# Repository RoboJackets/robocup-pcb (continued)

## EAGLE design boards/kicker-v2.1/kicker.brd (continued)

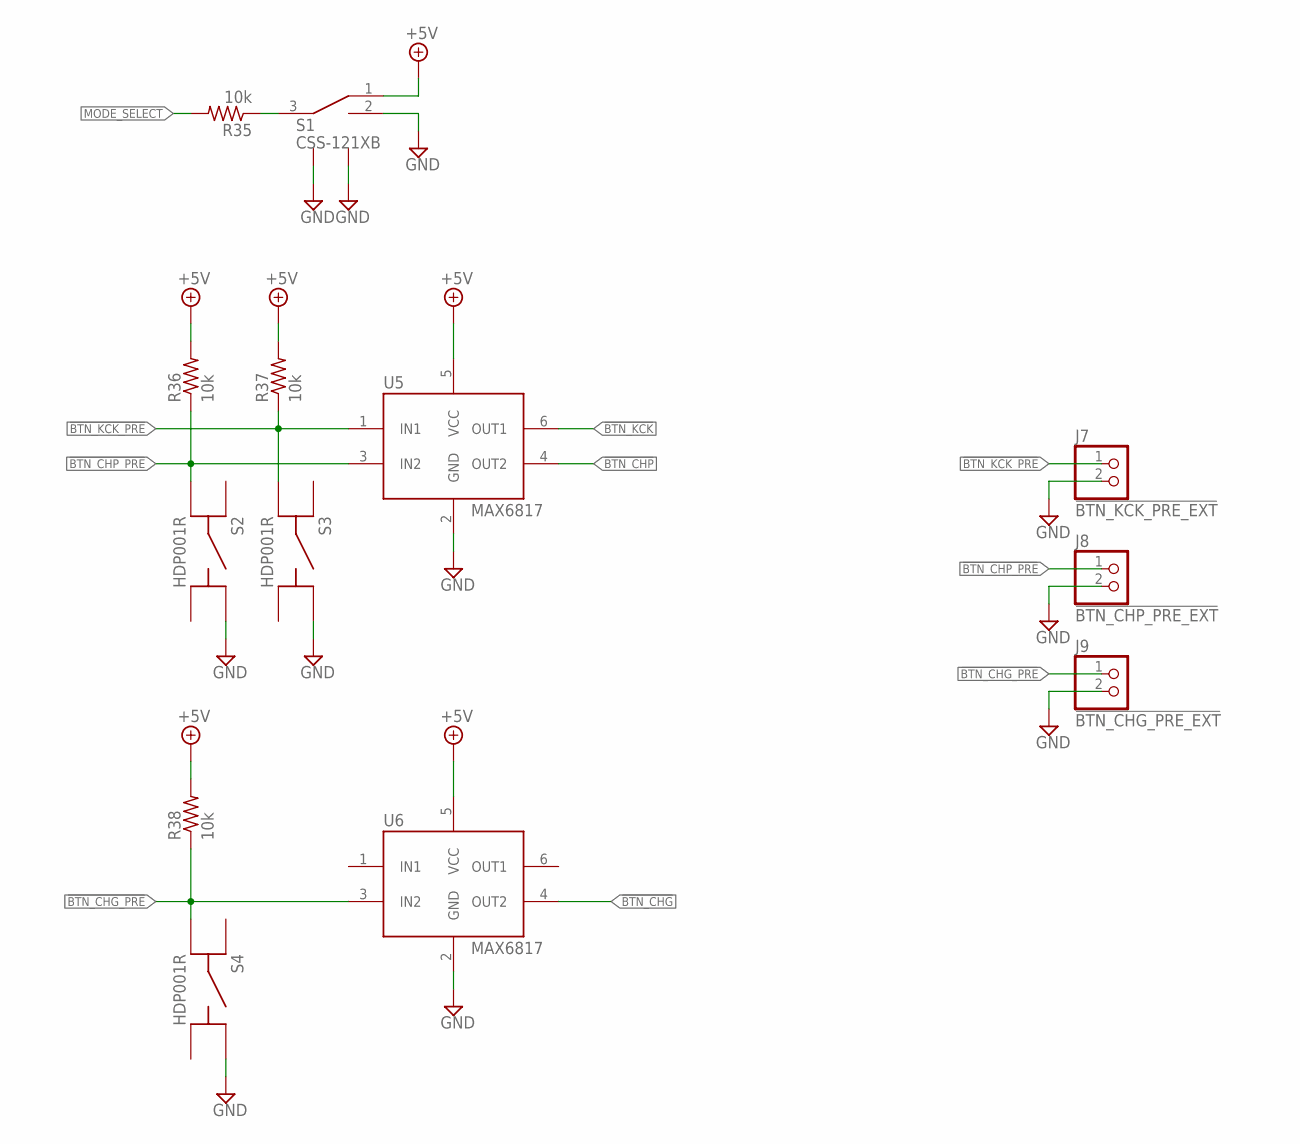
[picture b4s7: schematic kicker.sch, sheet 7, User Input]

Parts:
J7: !BTN_KCK_PRE_EXT; 1X2
J8: !BTN_CHP_PRE_EXT; 1X2
J9: !BTN_CHG_PRE_EXT; 1X2
R35, R36, R37, R38: 10k; R0603
S1: CSS-121XB
S2, S3, S4: HDP001R
U5, U6: MAX6817; SOT-23-6

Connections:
!BTN_CHG: U6.4 (OUT2); also elsewhere on the board
!BTN_CHG_PRE: J9.1, R38.1, S4.C (A2), U6.3 (IN2)
!BTN_CHP: U5.4 (OUT2); also elsewhere on the board
!BTN_CHP_PRE: J8.1, R36.1, S2.C (A2), U5.3 (IN2)
!BTN_KCK: U5.6 (OUT1); also elsewhere on the board
!BTN_KCK_PRE: J7.1, R37.1, S3.C (A2), U5.1 (IN1)
+5V: R36.2, R37.2, R38.2, S1.1 (A), U5.5 (VCC), U6.5 (VCC); also elsewhere on the board
GND: J7.2, J8.2, J9.2, S1.2 (B), S1.LEG1, S1.LEG4 (LEG2), S2.B (B1), S3.B (B1), S4.B (B1), U5.2 (GND), U6.2 (GND); also elsewhere on the board
MODE_SELECT: R35.2; also elsewhere on the board
unnamed: R35.1, S1.3 (COMMON)

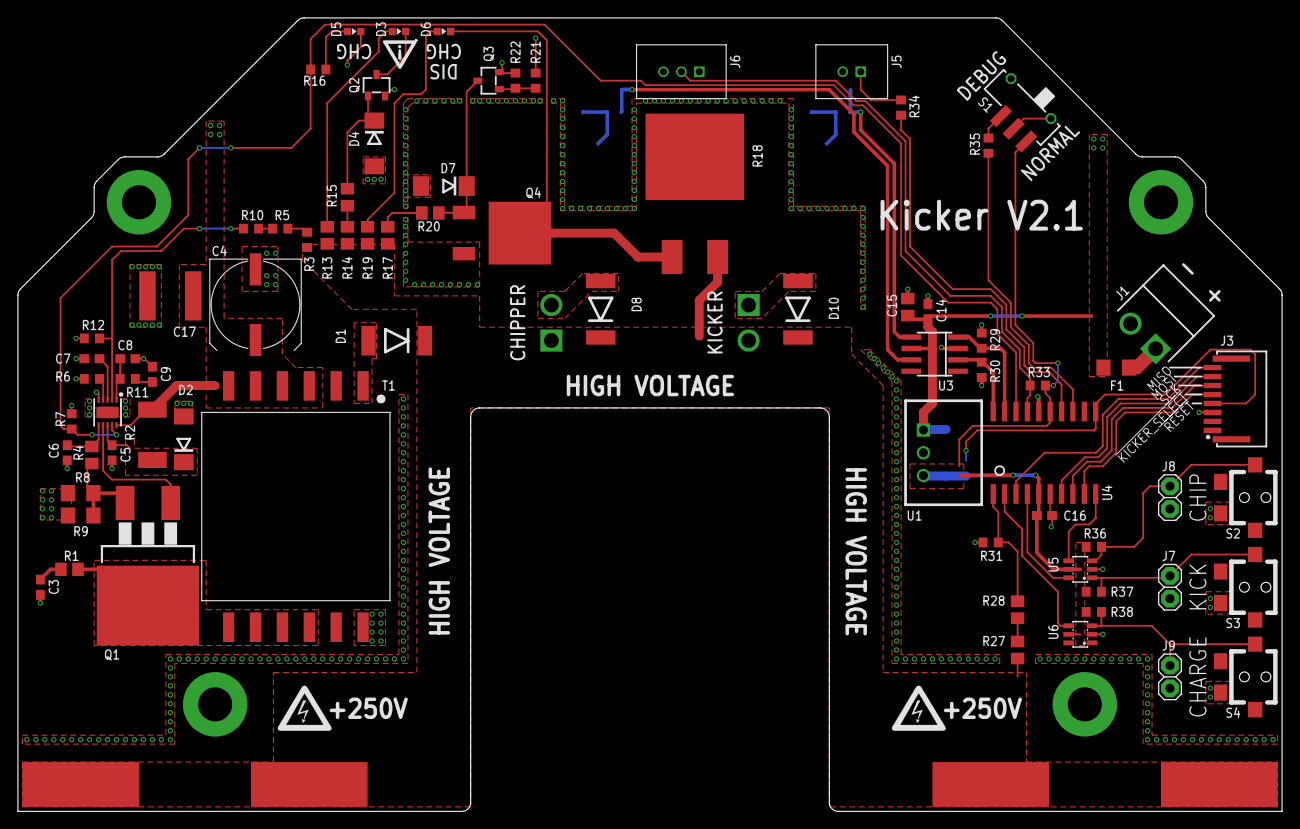
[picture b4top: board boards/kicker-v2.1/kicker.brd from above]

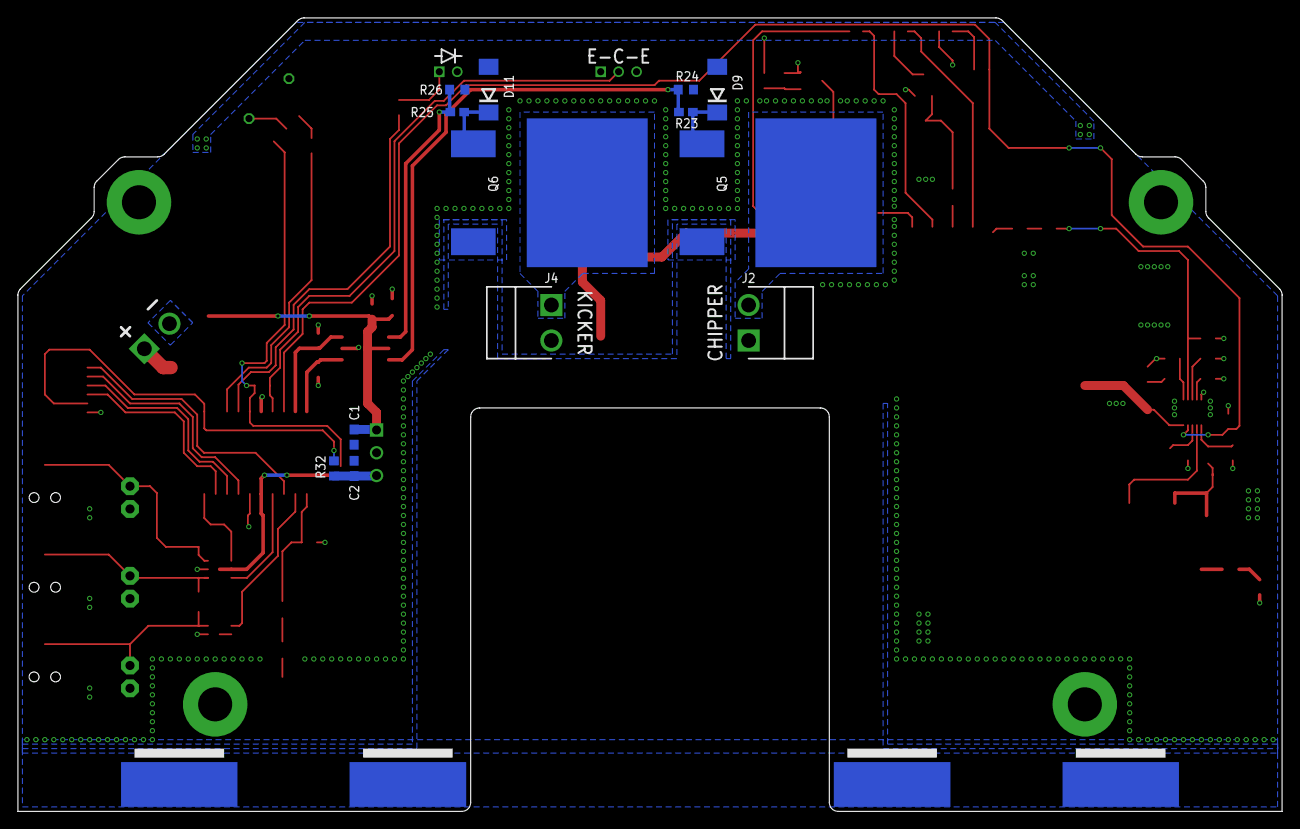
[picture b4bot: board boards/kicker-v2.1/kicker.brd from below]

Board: 2 copper layers, 141.0 x 88.5 mm, 96 parts (13 on the bottom side), 56 nets.

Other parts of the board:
U$1, U$2: HV_WARNING
U$4: WARNING2

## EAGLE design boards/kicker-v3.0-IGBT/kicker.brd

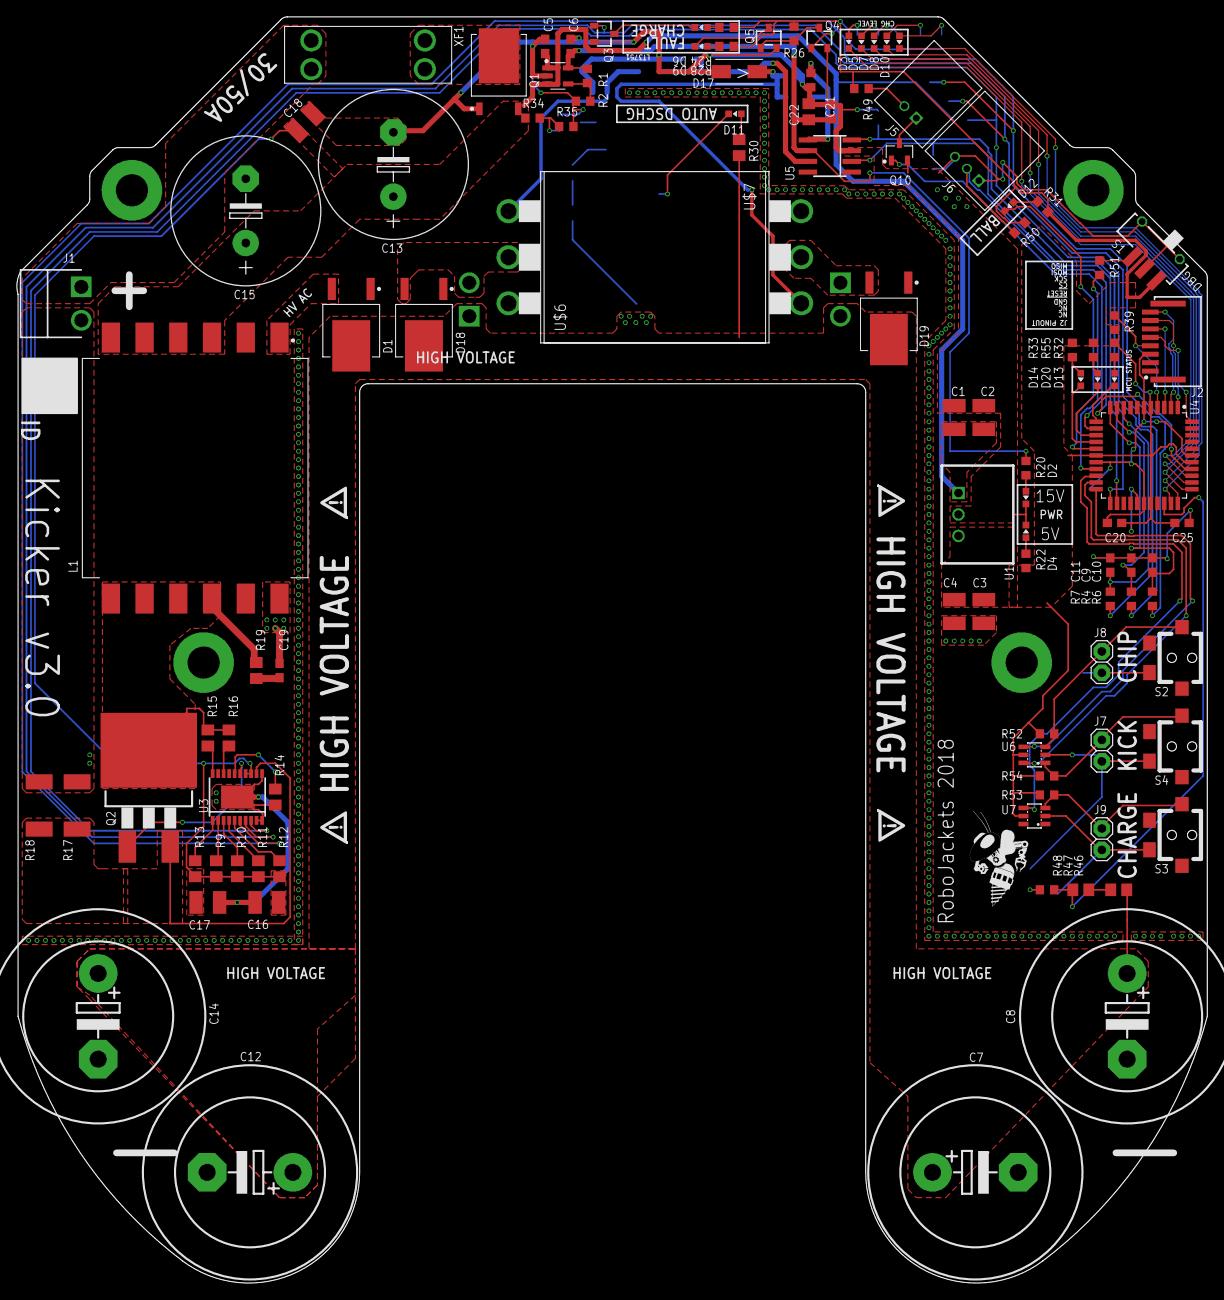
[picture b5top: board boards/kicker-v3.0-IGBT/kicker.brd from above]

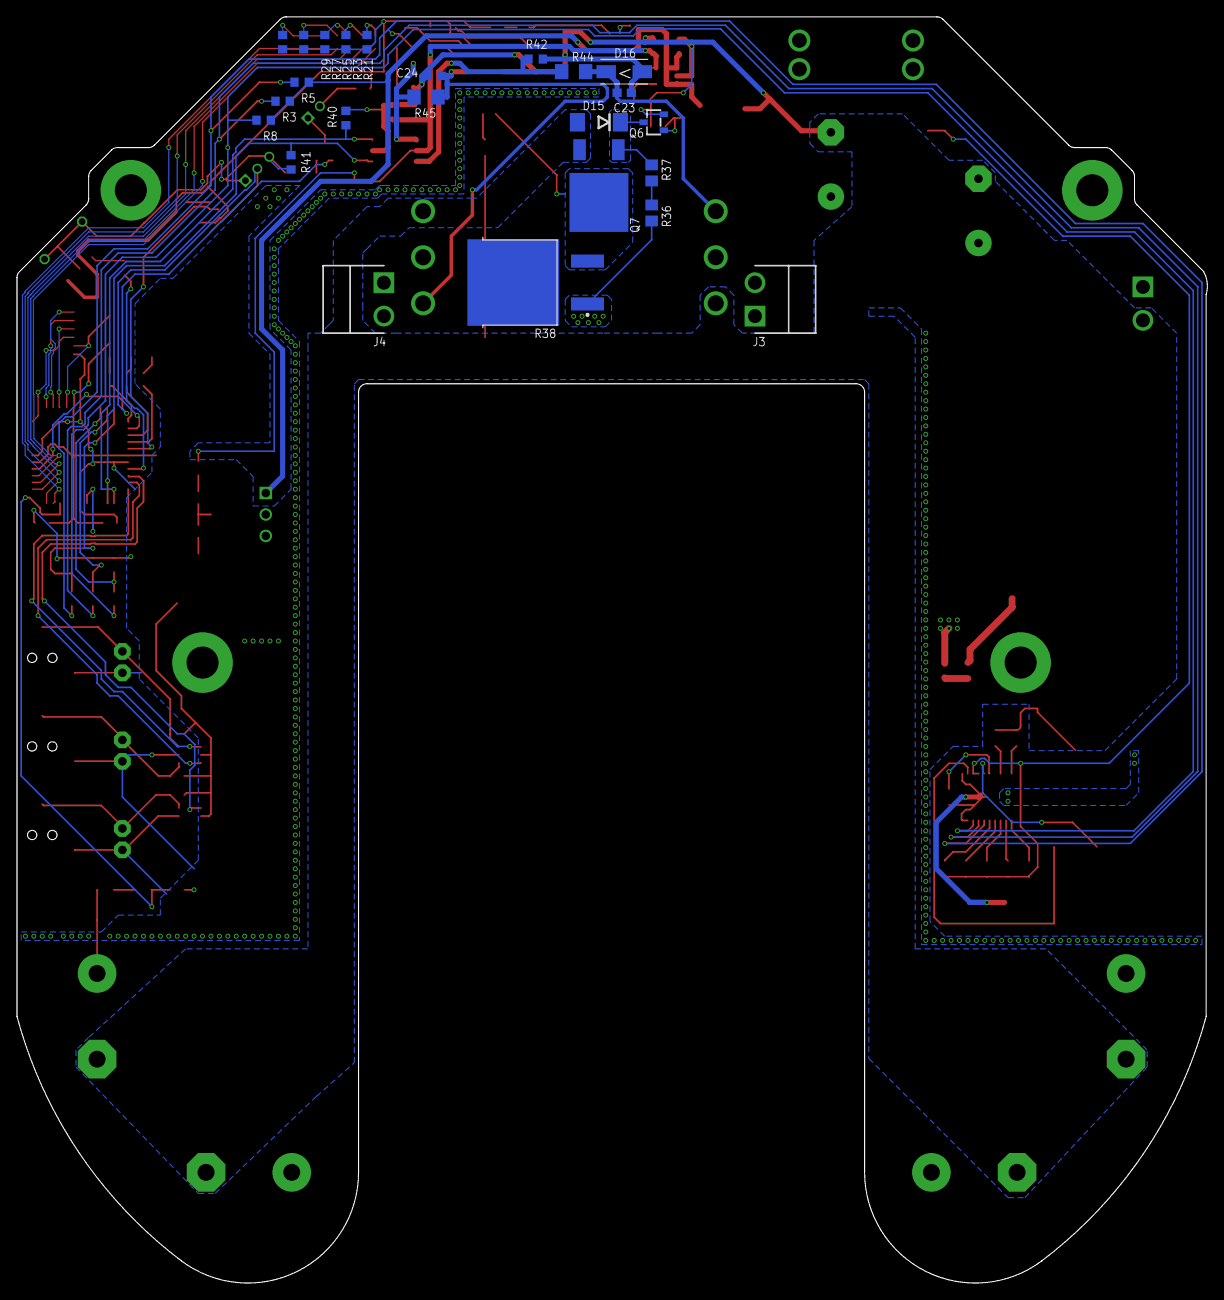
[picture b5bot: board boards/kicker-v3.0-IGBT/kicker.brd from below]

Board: 2 copper layers, 141.1 x 150.1 mm, 137 parts (24 on the bottom side), 84 nets.

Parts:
C1, C2: 4.7uf 35V; C1210
C3, C4: 4.7uf 16V; C1210
C5, C9, C10, C11: 1uF; C0603
C6: 2.2uF; C0603
C7, C8, C12, C14: 1000uF; EB25D
C13, C15: 560uF; E7,5-18
C16, C17, C18: 10uF (X7R); C1210
C19: 220pF 100V; C0603
C20, C25: 0.1uF; C0603
C21: 0.1uF 35V; C0603
C22: 22uF 35V; C0805
C23, C24: 0.1uF 50V; C0603
D1, D18, D19: VS-5EWH06FN-M3D-PAK_TO252AA; TO460P990X239-3
D2, D3, D4, D5, D6, D13: GREEN; CHIP-LED0603
D7, D11, D20: YELLOW; CHIP-LED0603
D8, D9, D10, D14: RED; CHIP-LED0603
D12: BLUE; CHIP-LED0603
D15: 3SMBJ5929B-TP; DO214AA
D16, D17: SMAJ20ADO-214AC; RESM5226X262
J1, J3, J4: B2PS-VH(LF)(SN); B2PS-CENTERED
J2: HFW8R-1ST
J5: 2-PIN_2MM-H; 2MM-2-H
J6: 3-PIN_2MM-H; 2MM-3-H
J7: !BTN_KCK_PRE_EXT; 1X2
J8: !BTN_CHP_PRE_EXT; 1X2
J9: !BTN_CHG_PRE_EXT; 1X2
L1: GA34XX-BLBL; SOP400P3370X1400-12
Q1: ATP302ATPAK; TO460P950X150-3
Q2: IRFS4227; D2PAK
Q3, Q4, Q5, Q6: BSS127; SOT-23-3
Q7: AOD1N60; DPAK
Q10: BSS806NSOT-23-3; SOT95P240X110-3
R1: 110k; R0603
R2, R39, R40, R41, R42, R43, R50, R51, R52, R53, R54: 10k; R0603
R3, R5, R8, R35: 100k; R0603
R4, R6, R7: 160; R0603
R9, R11: 294k 1%; R0805
R10, R12: 412k 1%; R0805
R13, R16: 40.2k 1%; R0805
R14: 1.62k 1%; R0805
R15: 18.2k 1%; R0805
R17, R18: 7.5m 1%; R2512
R19: 22; R0805
R20, R26: 1k; R0603
R21, R22, R23, R24, R32: 162; R0603
R25, R27, R28, R29, R33: 261; R0603
R30: ERJ-P06J274V; R0805
R31, R55: 60; R0603
R34: 270k; R0603
R36, R37, R46, R47: ERJ-6GEYJ515V; R0805
R38: 1.5k 35W; TO508P1539X450-3
R44, R45: 160; R1206
R48: RC0603FR-07205KL; R0603
R49: 50; R0603
S1: CSS-121XB
S2, S3, S4: HDP001R
U1: R-78E5.0-0.5; R-78E
U2: 15V; SOT95P280X145-5
U3: LT3751FE; TSSOP-20_EP
U4: AT32ATQFP44; QFP80P1200X1200X120-44
U5: IX4427N; SOIC-8
U6, U7: MAX6817; SOT-23-6
U$1, U$2, U$3, U$4: WARNING2
U$5: ROBOBUZZ_0.6X
U$6, U$7: IXGK400N30A3; TO264
XF1: 30A; 3557-2

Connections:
!BTN_CHG: U4.20, U7.4
!BTN_CHG_PRE: J9.1, R53.1, S3.C, U7.3
!BTN_CHP: U4.22, U6.4
!BTN_CHP_PRE: J8.1, R52.1, S2.C, U6.3
!BTN_KCK: U4.21, U6.6
!BTN_KCK_PRE: J7.1, R54.1, S4.C, U6.1
!DONE!: C9.1, R4.1, U4.10
!DONE_LPF: Q3.1, R3.1, R4.2, U3.7
!FAULT!: C10.1, R6.1, U4.11
!FAULT_LPF: Q4.1, R5.1, R6.2, U3.6
!KICKER_SELECT: J2.5, U4.44
!RESET: J2.4, R39.1, U4.4
+5V: C3.1, C4.1, C20.2, C25.2, R21.2, R22.2, R23.2, R24.2, R25.2, R26.2, R27.2, R28.2, R29.2, R31.2, R32.2, R33.2, R39.2, R49.1, R50.2, R52.2, R53.2, R54.2, R55.2, S1.1, U1.3, U4.5, U4.17, U4.27, U4.29, U4.38, U6.5, U7.5
+15.0V: C6.1, C21.2, C22.2, R1.2, R20.2, U2.5, U5.6
BALL_SENSE: D12.C, U4.16
BB_RX: J6.2, R50.1, U4.37
BB_TX: Q10.1, U4.13
CHARGE: C11.1, R7.1, U4.9
CHARGE_LPF: R7.2, R8.1, U3.8
CHIP: R41.2, U4.24, U5.2
CHIPPER: D18.2, J3.2, U$7.C_BOT
CHIP_GATE: R42.2, R44.1, U5.7
DISCHARGE_DRAIN: D11.C, Q7.FIN, R38.2
GND: C1.2, C2.2, C3.2, C4.2, C5.2, C6.2, C7.-, C8.-, C9.2, C10.2, C11.2, C12.-, C13.-, C14.-, C15.-, C16.1, C17.1, C18.1, C19.2, C20.1, C21.1, C22.1, C23.2, C24.2, C25.1, D2.C, D4.C, D15.A, D16.1, D17.1, J1.2, J2.3, J6.1, J6.3, J7.2, J8.2, J9.2, L1.12, Q1.1, Q3.2, Q4.2, Q5.2, Q6.2, Q7.3, Q10.2, R2.1, R14.2, R17.1, R18.1, R35.1, R40.1, R41.1, R42.1, R43.1, R48.1, S1.2, S1.LEG1, S1.LEG4, S2.B, S3.B, S4.B, U1.2, U2.2, U3.9, U3.10, U3.11, U3.PAD, U4.6, U4.18, U4.28, U4.39, U5.3, U6.2, U7.2, U$6.E_BOT, U$7.E_BOT
HVGATE: Q2.1, U3.15
HV_AC: D1.2, L1.1
HV_IND_HIGH: D8.C, U4.33
HV_IND_LOW: D5.C, U4.35
HV_IND_MAX: D10.C, U4.32
HV_IND_MID: D7.C, U4.34
HV_IND_MIN: D3.C, U4.36
KICK: R40.2, U4.23, U5.4
KICKER: D19.2, J4.1, U$6.C_BOT
KICK_GATE: R43.2, R45.1, U5.5
MCU_ERR: D14.C, U4.15
MCU_INIT_OK: D13.C, U4.12
MCU_MODE: D20.C, U4.14
MISO: J2.8, U4.2
MODE_SELECT: R51.2, U4.19
MOSI: J2.7, U4.1
unnamed: R14.1, U3.16
unnamed: R36.1, R37.2
unnamed: D14.A, R33.1
unnamed: D13.A, R32.1
unnamed: D6.A, R24.1
unnamed: J5.2, R49.2
unnamed: C23.1, D16.2, R44.2, U$7.G_BOT
unnamed: C24.1, D17.2, R45.2, U$6.G_BOT
unnamed: Q1.3, XF1.3, XF1.4
unnamed: Q6.1, R34.1, R35.2
unnamed: D3.A, R21.1
unnamed: D5.A, R23.1
unnamed: D7.A, R25.1
unnamed: R51.1, S1.3
unnamed: R46.1, R47.2
unnamed: R1.1, R2.2, U2.4
unnamed: D20.A, R55.1
unnamed: J5.1, Q10.3
unnamed: D4.A, R22.1
unnamed: D8.A, R27.1
unnamed: D2.A, R20.1
unnamed: R13.1, U3.1
unnamed: Q4.3, Q5.1, R26.1
unnamed: D9.A, R28.1
unnamed: D9.C, Q5.3
unnamed: D11.A, R30.1
unnamed: D10.A, R29.1
unnamed: C19.1, R19.1
unnamed: D6.C, Q3.3
unnamed: J1.1, XF1.1, XF1.2
unnamed: D12.A, R31.1
OVLO1: R10.2, U3.3
OVLO2: R12.2, U3.5
QUICK_DISCHARGE: D15.C, Q6.3, Q7.1, R37.1
RDCM: R15.2, U3.20
RVOUT: R16.2, U3.18
SCK: J2.6, U4.3
SENSE: Q2.3, R17.2, R18.2, U3.12
UVLO1: R9.2, U3.2
UVLO2: R11.2, U3.4
V+: C7.+, C8.+, C12.+, C14.+, D1.3, D18.3, D19.3, J3.1, J4.2, R30.2, R36.2, R38.1, R46.2
VBATT: C1.1, C2.1, C5.1, C13.+, C15.+, C16.2, C17.2, C18.2, L1.3, L1.4, L1.5, L1.6, Q1.2, R3.2, R5.2, R8.2, R9.1, R10.1, R11.1, R12.1, R13.2, R34.2, U1.1, U2.1, U2.3, U3.13, U3.14
VMON: R47.1, R48.2, U4.31
VSN: L1.7, L1.8, L1.9, L1.10, Q2.2, R15.1, R16.1, R19.2
